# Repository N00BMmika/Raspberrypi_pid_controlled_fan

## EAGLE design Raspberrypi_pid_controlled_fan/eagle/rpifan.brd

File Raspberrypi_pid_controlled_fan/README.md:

# Raspberry Pi 4 fan controller

Raspberry Pi 4 PID controlled cooling.

## Parts 
I purchased this [case with fans](https://www.amazon.com/Raspberry-Acrylic-Cooling-Install-Magnetic/dp/B07WTWKQKT) from local store.

By default fan is connected to +5V e.g. it is all the time on.

This causes continuous noise.

There are several instructions for making temperature controlled fan where the fan speed is dependent on the CPU temperature. For example this good one: [Variable Speed Cooling Fan for Raspberry Pi using PWM ](https://www.sensorsiot.org/variable-speed-cooling-fan-for-raspberry-pi-using-pwm-video138/)

Additional requrement I had was that I wanted to:
- get the control HW inside the case.
- stop the fan if CPU is not too hot and make the fan as silent as possible.

Since I was not able to find good instructions for thse needs, I needed to go into DIY mode. Based on above example I made design with [Eagle](https://www.autodesk.com/products/eagle/overview). 

Parts used in design are:
- MOSFET : 2N7000
- resistor : 100k
- capacitor : 100uF
- 12 pin female connector
- diode : skipped (even added to design)

Capacitor and high  frequency (200Hz) PWM makes the PWM output closer to DAC output. This reduces noise of the motor when it is driven with PWM. 

## HW 
Design was done with [Eagle](https://www.autodesk.com/products/eagle/free-download). Here are [board](eagle/rpifan.brd) and [schema](eagle/rpifan.sch) files.

Top view of the designed board looks like this.

.

Trick to make the assembly and soldering easier is to cut legs 3,5 and 11 away from the 12 pin female connector. This way traces to pins 4,6,12 are easier to make.

3D-visualization exported from Eagle to [Fusion360](https://www.autodesk.com/campaigns/fusion-360-for-hobbyists)

Actual assembly looks almost 1:1 the same :) 

NOTE: FET is oriented differently in the actual assembly due mistake. Some rework was required to solder FET legs properly.

Fan control board inside the Case

Case did not close properly since fan on top cover goes lower than the top cover. The case is parts are put together with magnets so it was possible to solve the issue with four ~2mm thick round magnets which where put between case magnets (yellow arrows).

## SW 
Control SW was made with [Node Red](https://nodered.org/) which is pre-installed in Raspbian. [Node Red Dashboard](https://flows.nodered.org/node/node-red-dashboard) must be installed for the fan control flow.

CPU temperature reading was done with modified version of [Raspberry Pi Control Dashboard](https://flows.nodered.org/flow/25af5334a79d6c02d6413968a8bff572). 

There are separate flows for reading temperature

Controlling the FAN

and for logging (off by default)

Logging of CPU temperature, CPU load and fan PWM is for later analysis of the PID functionality. There is also Node Red Dashboard GUI showing CPU tepmerature, PID output and PID internal paramters. It could help to tune PID parameters.

All flows are [here](flow/flow.json)

The code in PID controller node is following:
```js
setPoint = 60 // Target temperature
p = 2         // Proportional
i = 0.5       // Integral
d = 0.1       // Derivative
integral=context.get('integral') || 0 
lastTemperature = context.get('last') || setPoint

temperature = msg.payload
error = setPoint - temperature
proportional = p * error
integral = integral + i * error

// Limits for integral value
if (integral<-100){
    integral=-100
} 
if (integral > 100){
    integral = 100
}

dtemp = temperature - lastTemperature

derivative = d * dtemp

context.set('last',temperature)
context.set('integral',integral)

output = proportional + integral + derivative

// Limits for output value. 
// FAN can only reduce temperature
if (output<0){
    output=0
} else if (output > 100){
    output = 100
}

msg.payload = 100-output

return [msg, 
    {"payload": integral},
    {"payload": derivative}
]
```
Target temperature (`setPoint`) is set to 60 &deg;C so fan is not running if CPU load is low.

Attention can be paid also to "pid to pwn" node where 0-100 PID output is scaled to suitable PWM duty cycle. My fan started reliably with 50% duty cycle so PID output was changed from 0-100 to 0,50-100.

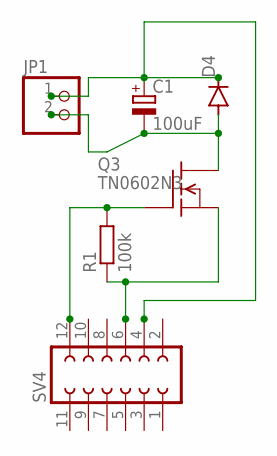
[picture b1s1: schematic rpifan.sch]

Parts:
C1: 100uF; E2-5
D4: DIODE-D-2.5; D-2.5
JP1: PINHD-1X2; 1X02
Q3: TN0602N3; TO-92
R1: 100k; 0204/7
SV4: FE06-2

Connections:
unnamed: Q3.2 (G), R1.2, SV4.12
unnamed: Q3.1 (S), R1.1, SV4.6
unnamed: C1.-, D4.A, JP1.2, Q3.3 (D)
unnamed: C1.+, D4.C, JP1.1, SV4.4

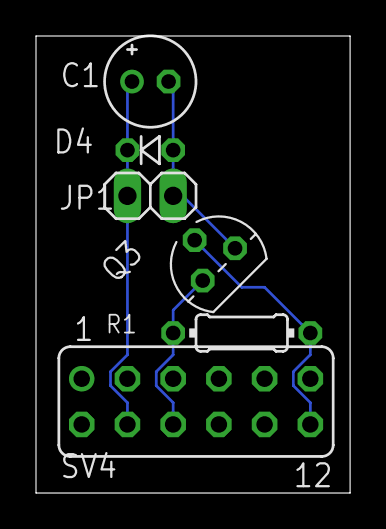
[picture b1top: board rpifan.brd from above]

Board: 2 copper layers, 17.4 x 25.4 mm, 6 parts (0 on the bottom side), 4 nets.

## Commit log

2020-04-17 project published
2020-04-17 typo fixes
2020-04-17 text & image alignments
2020-04-17 even more type fixes
